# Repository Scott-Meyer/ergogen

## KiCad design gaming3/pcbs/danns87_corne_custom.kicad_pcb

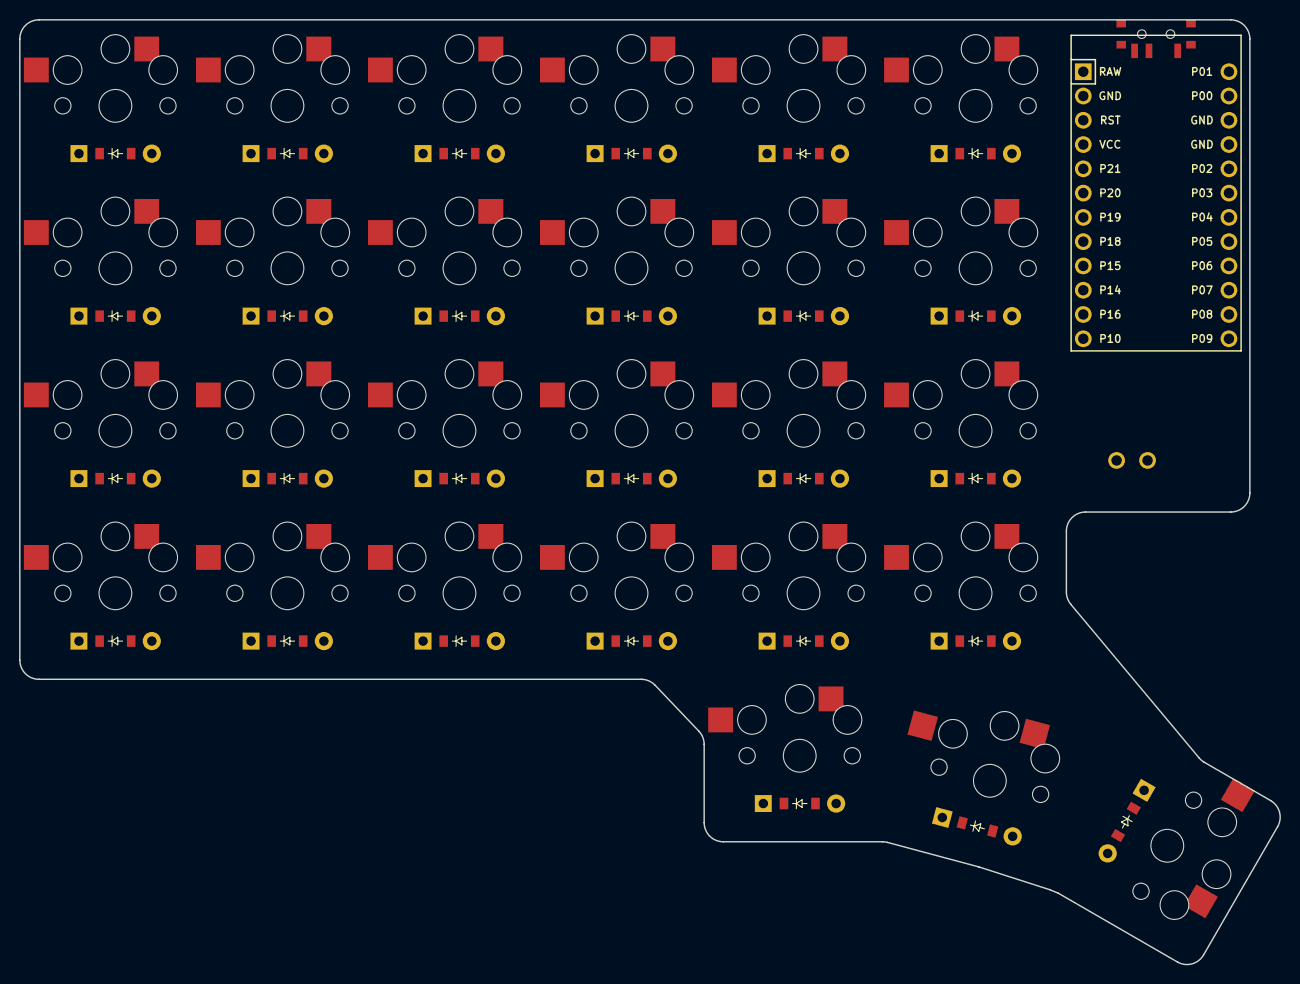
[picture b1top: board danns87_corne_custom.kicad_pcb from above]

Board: 2 copper layers, 131.9 x 98.8 mm, 55 parts (0 on the bottom side), 39 nets, no tracks yet.

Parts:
D1, D2, D3, D4, D5, D6, D7, D8, D9, D10, D11, D12, D13, D14, D15, D16, D17, D18, D19, D20, D21, D22, D23, D24, D25, D26, D27: ComboDiode
MCU1: ProMicro
S1, S2, S3, S4, S5, S6, S7, S8, S9, S10, S11, S12, S13, S14, S15, S16, S17, S18, S19, S20, S21, S22, S23, S24, S25, S26, S27: PG1350

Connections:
GND: MCU1.2, MCU1.15, MCU1.16
P3: D4.1, D4.2, D8.1, D8.2, D12.1, D12.2, D16.1, D16.2, D20.1, D20.2, D24.1, D24.2, MCU1.18
P4: D3.1, D3.2, D7.1, D7.2, D11.1, D11.2, D15.1, D15.2, D19.1, D19.2, D23.1, D23.2, MCU1.19
P5: D2.1, D2.2, D6.1, D6.2, D10.1, D10.2, D14.1, D14.2, D18.1, D18.2, D22.1, D22.2, MCU1.20
P6: D1.1, D1.2, D5.1, D5.2, D9.1, D9.2, D13.1, D13.2, D17.1, D17.2, D21.1, D21.2, MCU1.21
P7: D25.1, D25.2, D26.1, D26.2, D27.1, D27.2, MCU1.22
P14: MCU1.10, S21.2, S22.2, S23.2, S24.2, S27.2
P15: MCU1.9, S17.2, S18.2, S19.2, S20.2, S26.2
P18: MCU1.8, S13.2, S14.2, S15.2, S16.2, S25.2
P19: MCU1.7, S9.2, S10.2, S11.2, S12.2
P20: MCU1.6, S5.2, S6.2, S7.2, S8.2
P21: MCU1.5, S1.2, S2.2, S3.2, S4.2
far_thumb: D27.1, D27.2, S27.1
home_thumb: D26.1, D26.2, S26.1
index_bottom: D17.1, D17.2, S17.1
index_home: D18.1, D18.2, S18.1
index_third: D19.1, D19.2, S19.1
index_top: D20.1, D20.2, S20.1
inner_bottom: D21.1, D21.2, S21.1
inner_home: D22.1, D22.2, S22.1
inner_third: D23.1, D23.2, S23.1
inner_top: D24.1, D24.2, S24.1
middle_bottom: D13.1, D13.2, S13.1
middle_home: D14.1, D14.2, S14.1
middle_third: D15.1, D15.2, S15.1
middle_top: D16.1, D16.2, S16.1
near_thumb: D25.1, D25.2, S25.1
outer_bottom: D1.1, D1.2, S1.1
outer_home: D2.1, D2.2, S2.1
outer_third: D3.1, D3.2, S3.1
outer_top: D4.1, D4.2, S4.1
pinky_bottom: D5.1, D5.2, S5.1
pinky_home: D6.1, D6.2, S6.1
pinky_third: D7.1, D7.2, S7.1
pinky_top: D8.1, D8.2, S8.1
ring_bottom: D9.1, D9.2, S9.1
ring_home: D10.1, D10.2, S10.1
ring_third: D11.1, D11.2, S11.1
ring_top: D12.1, D12.2, S12.1

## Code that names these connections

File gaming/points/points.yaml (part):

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        skip: false
        asym: both
        name: matrix_pinky_bottom
        colrow: pinky_bottom
        col: &ref_1
            stagger: 0
            spread: 19
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        skip: false
        asym: both
        name: matrix_pinky_home
        colrow: pinky_home
        col: *ref_1
        row: home
        mirrored: false
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        skip: false
        asym: both
        name: matrix_pinky_top
        colrow: pinky_top
        col: *ref_1
        row: top
        mirrored: false
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
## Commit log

2022-02-15 Progress but havn't worked on it in days so I want to save.
2022-11-06 Everything local
2022-11-23 Potential
2022-12-01 keyboard progress
